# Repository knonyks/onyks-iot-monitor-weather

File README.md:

<span style="font-weight:700;font-size:40px; font-style: italic;">
    Stacja pogodowa
</span>

## Wstęp
Tematem tego projektu jest stacja pogodowa, która zbiera informację odnośnie warunków atmosferycznych i na ich podstawie wysyła dane na oficjalną stronę koła naukowego ONYKS. Stacja ta, mierzy takie wielkości jak poziom CO2, temperaturę, prędkość wiatru, wilgotność itp. (o tym dalej).

## Założenia - jak to ma działać
Dane zbierane są za pomocą odpowiednich czujników a następnie przetwarzane przez mikrokontroler ESP32 - w tym projekcie użyto ESP32-WROOM-32D. Po przetworzeniu dane będą wysyłane na serwer przy użyciu WIFI, a następnie wyświetlane w odpowiedniej rubryce na głównej stronie koła naukowego ONYKS. Planowany rozmiar PCB ***100 mm x 82 mm***.

## Pomiary 

- Pomiar prędkości wiatru - polega na zmierzeniu prędkości obrotowej wału z magnesem, który jest obracany przy użyciu wiatraka. Pomiar ten będzie wykonywany za pomocą **Hallotronu** (czyli na przykład pomiar częstotliwości umownej "1" na czujniku i na podstawie tego określenie prędkości).

- Pomiar ilości opadów - wykonywany w podobny sposób co pomiar prędkości wiatru, z tą różnicą, że wałem kręcą łopatki, o konkretnej objętości. Takie koło wodne wporowadzane jest w ruch kiedy dana łopatka jest wypełniona. Obroty wału z magnesem są szczytywane za pomocą **Hallotronu**. 

- Pomiar kierunku wiatru - odbywa się również za pomocą 4 **Hallotronów** i wału obracanego wiatrowskazem. Tym razem aktywne czujniki wskazują kierunek. Do wskazania będzie 8 kierunków (na przykład pólnoc, południowy wschód itd.).

- Pomiar temperatury oraz wilgotności powietrza - odczytywane dane są z czujnika **DHT22**, który jest zamontowany w obudowie na zewnątrz stacji.

- Pomiar stężenia C02 w atmosferze - odbywa się za pomocą czujnika **SEN0219** znajdującego się bezpośrednio na PCB.

- Pomiar jakości powietrza - polega zastosowaniu czujnika **MQ135**, który jest czuły na Amoniak, gazy Siarczku, opary spowodowane spalaniem Benzenu, oraz potrafi wykrywać dym i innego rodzaju szkodliwe gazy. W czystym powietrzu czujnik ten ma niską przewodność, rośnie wraz z pojawieniem się w atmosferze substancji szkodliwych

## Obudowy oraz elementy mechaniczne

- Obudowy, będą zaprojektowane w oprogramowaniu CAD a następnie wyprodukowane za pomocą druku 3D. 

- Wały i łożyska będą kupowane w sklepie modelarskim np. *https://sklep.modelarnia.pl/*, lub budowalnym takim jak OBI czy CASTORAMA.

- Wiatrak i koło wodne będą zaprojektowane w oprogramowaniu CAD, a następnie drukowane.

- Do **Hallotronów** będą użyte drobne magnesy Neodymowe

## Schematy blokowe

###  Położenie elementów na płytce drukowanej :

###  Ogólny schemat ideowy układu :

## Link do rozpiski z elementami
Tutaj stworzony jest wykaz elementów potrzebnych do złożenia danej stacji : 
https://docs.google.com/spreadsheets/d/16E9U7lwzSHfPhs8wRjM2mrblf8zyNPCpttjlwKn6Azs/edit?usp=sharing

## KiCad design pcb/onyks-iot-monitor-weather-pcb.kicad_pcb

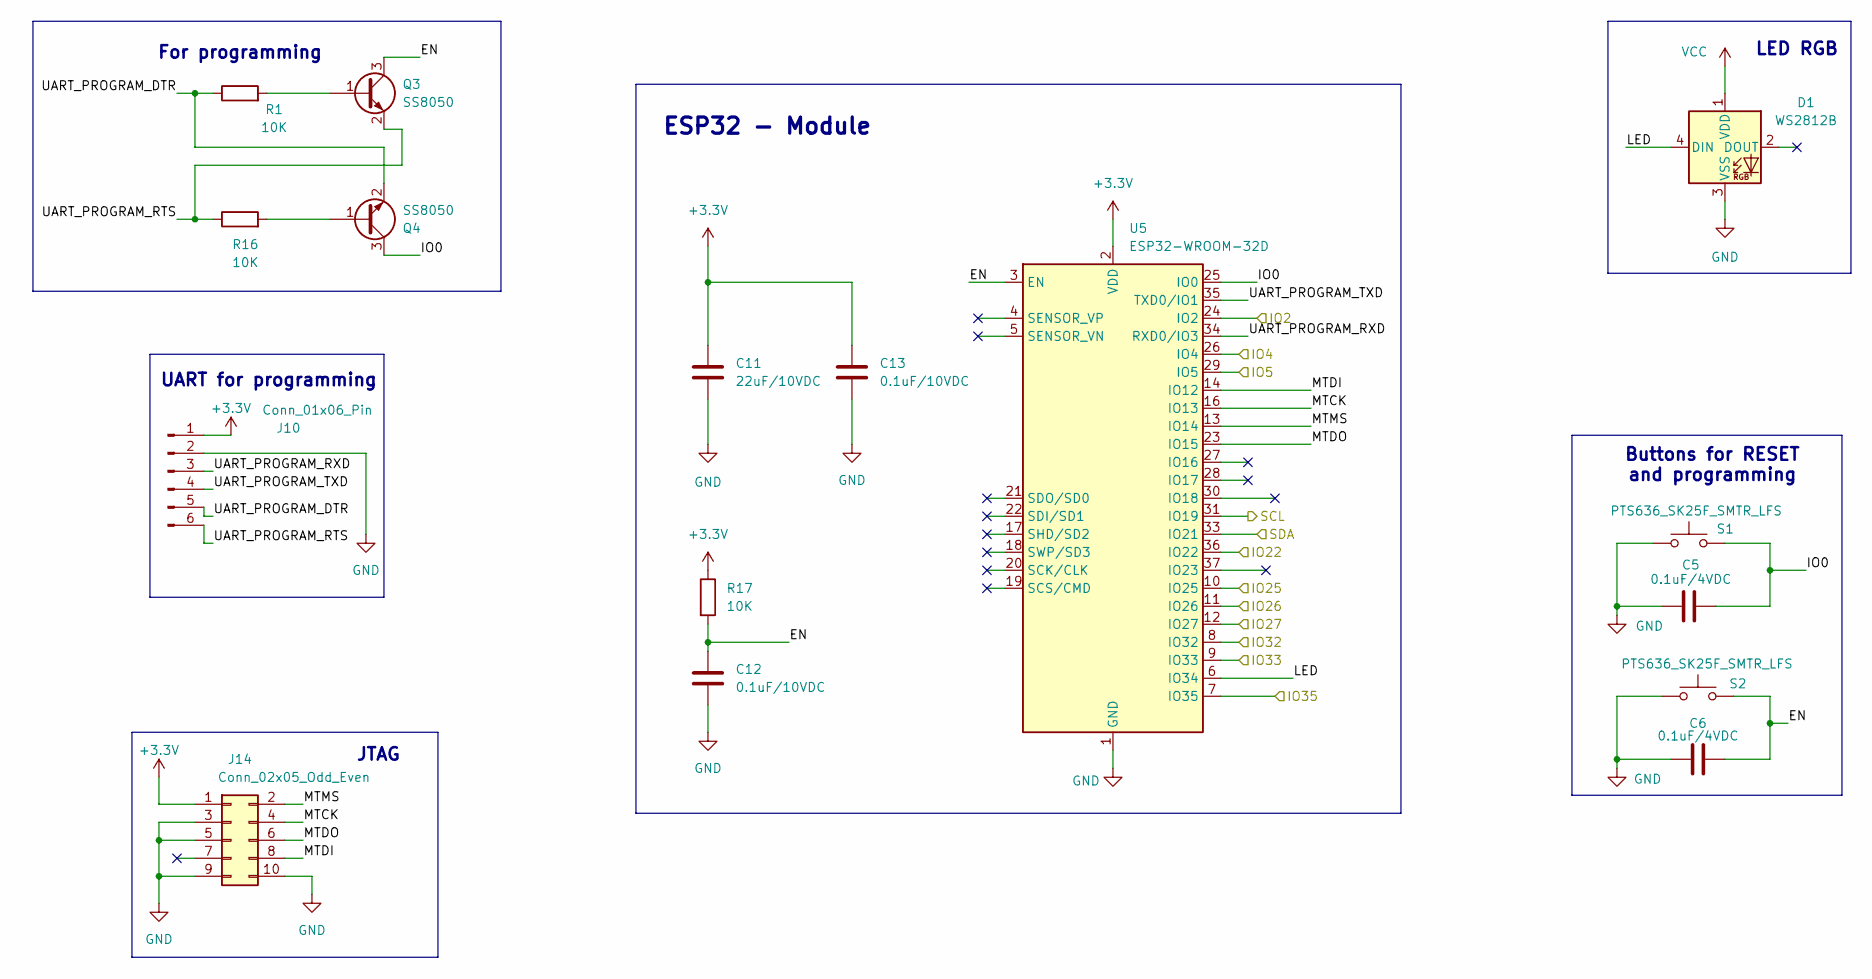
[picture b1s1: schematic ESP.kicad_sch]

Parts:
C5, C6: 0.1uF/4VDC; C_0603_1608Metric
C11: 22uF/10VDC; C_0603_1608Metric
C12, C13: 0.1uF/10VDC; C_0603_1608Metric
D1: WS2812B; LED_WS2812B_PLCC4_5.0x5.0mm_P3.2mm
J10: Conn_01x06_Pin; PinHeader_1x06_P2.54mm_Vertical
J14: Conn_02x05_Odd_Even; PinHeader_2x05_P2.54mm_Vertical
Q3, Q4: SS8050; SOT-23
R1, R16, R17: 10K; R_0603_1608Metric
S1, S2: PTS636_SK25F_SMTR_LFS; PTS636SK25FSMTRLFS; Mouser Part Number 611-PTS636SK25FSMTRL
U5: ESP32-WROOM-32D

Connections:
+3.3V: C11.1, C13.1, J10.1, J14.1, R17.1, U5.2 (VDD); also elsewhere on the board
/ESP32/EN: C6.2, C12.1, Q3.3 (C), R17.2, S2.2, U5.3 (EN)
/ESP32/IO0: C5.2, Q4.3 (C), S1.2, U5.25 (IO0)
/ESP32/IO2: U5.24 (IO2); also elsewhere on the board
/ESP32/IO4: U5.26 (IO4); also elsewhere on the board
/ESP32/IO5: U5.29 (IO5); also elsewhere on the board
/ESP32/IO22: U5.36 (IO22); also elsewhere on the board
/ESP32/IO25: U5.10 (IO25); also elsewhere on the board
/ESP32/IO26: U5.11 (IO26); also elsewhere on the board
/ESP32/IO27: U5.12 (IO27); also elsewhere on the board
/ESP32/IO32: U5.8 (IO32); also elsewhere on the board
/ESP32/IO33: U5.9 (IO33); also elsewhere on the board
/ESP32/IO35: U5.7 (IO35); also elsewhere on the board
/ESP32/LED: D1.4 (DIN), U5.6 (IO34)
/ESP32/MTCK: J14.4, U5.16 (IO13)
/ESP32/MTDI: J14.8, U5.14 (IO12)
/ESP32/MTDO: J14.6, U5.23 (IO15)
/ESP32/MTMS: J14.2, U5.13 (IO14)
/ESP32/SCL: U5.31 (IO19); also elsewhere on the board
/ESP32/SDA: U5.33 (IO21); also elsewhere on the board
/ESP32/UART_PROGRAM_DTR: J10.5, Q4.2 (E), R1.1
/ESP32/UART_PROGRAM_RTS: J10.6, Q3.2 (E), R16.1
/ESP32/UART_PROGRAM_RXD: J10.3, U5.34 (RXD0/IO3)
/ESP32/UART_PROGRAM_TXD: J10.4, U5.35 (TXD0/IO1)
GND: C5.1, C6.1, C11.2, C12.2, C13.2, D1.3 (VSS), J10.2, J14.3, J14.5, J14.9, J14.10, S1.1, S2.1, U5.1 (GND), U5.15 (GND), U5.38 (GND), U5.39 (GND); also elsewhere on the board
unnamed: Q3.1 (B), R1.2
unnamed: Q4.1 (B), R16.2
VCC: D1.1 (VDD); also elsewhere on the board

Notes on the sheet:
ESP32 - Module
JTAG
UART for programming
LED RGB
Buttons for RESET and programming
For programming

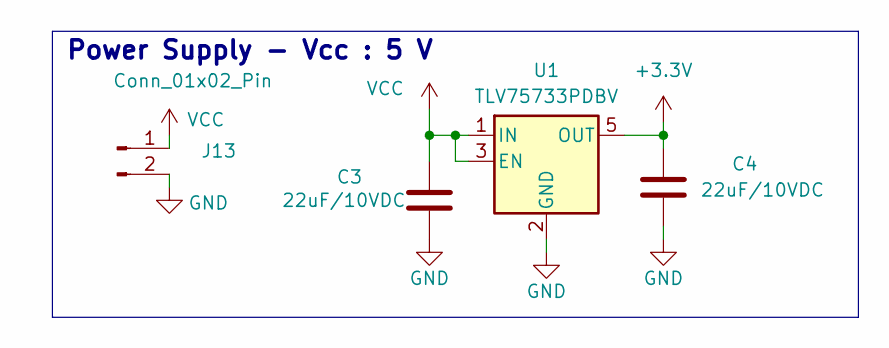
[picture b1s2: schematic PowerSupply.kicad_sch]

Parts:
C3, C4: 22uF/10VDC; C_0603_1608Metric
J13: Conn_01x02_Pin; PinHeader_1x02_P2.54mm_Vertical
U1: TLV75733PDBV; SOT-23-5

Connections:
+3.3V: C4.1, U1.5 (OUT); also elsewhere on the board
GND: C3.2, C4.2, J13.2, U1.2 (GND); also elsewhere on the board
VCC: C3.1, J13.1, U1.1 (IN), U1.3 (EN); also elsewhere on the board

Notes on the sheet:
Power Supply - Vcc : 5 V

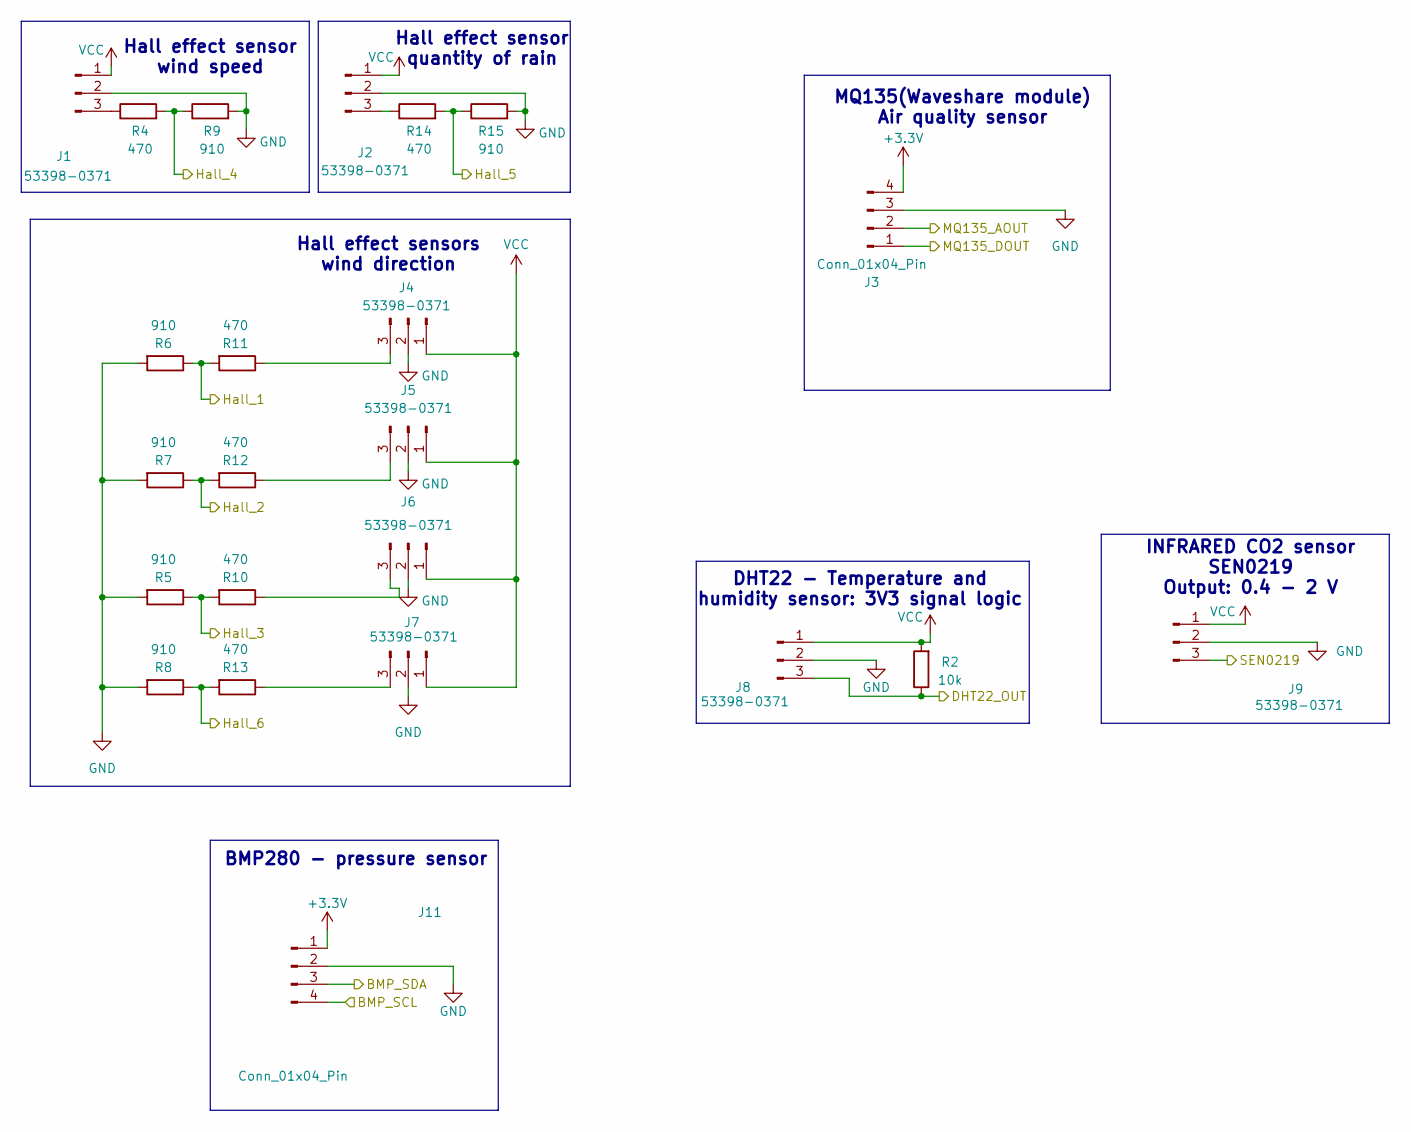
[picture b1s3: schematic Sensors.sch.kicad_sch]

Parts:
J1, J2, J4, J5, J6, J7, J8, J9: 53398-0371; PinHeader_1x03_P2.54mm_Vertical; Manufacturer_Part_Number 53398-0371
J3, J11: Conn_01x04_Pin; PinHeader_1x04_P2.54mm_Vertical
R2: 10k; R_0603_1608Metric
R4, R10, R11, R12, R13, R14: 470; R_0603_1608Metric
R5, R6, R7, R8, R9, R15: 910; R_0603_1608Metric

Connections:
+3.3V: J3.4, J11.1; also elsewhere on the board
/ESP32/IO2: J3.2; also elsewhere on the board
/ESP32/IO4: J8.3, R2.1; also elsewhere on the board
/ESP32/IO5: J9.3; also elsewhere on the board
/ESP32/IO22: J3.1; also elsewhere on the board
/ESP32/IO25: R6.1, R11.2; also elsewhere on the board
/ESP32/IO26: R7.1, R12.2; also elsewhere on the board
/ESP32/IO27: R5.1, R10.2; also elsewhere on the board
/ESP32/IO32: R4.2, R9.1; also elsewhere on the board
/ESP32/IO33: R8.1, R13.2; also elsewhere on the board
/ESP32/IO35: R14.2, R15.1; also elsewhere on the board
/ESP32/SCL: J11.4; also elsewhere on the board
/ESP32/SDA: J11.3; also elsewhere on the board
GND: J1.2, J2.2, J3.3, J4.2, J5.2, J6.2, J7.2, J8.2, J9.2, J11.2, R5.2, R6.2, R7.2, R8.2, R9.2, R15.2; also elsewhere on the board
unnamed: J1.3, R4.1
unnamed: J2.3, R14.1
unnamed: J4.3, R11.1
unnamed: J5.3, R12.1
unnamed: J6.3, R10.1
unnamed: J7.3, R13.1
VCC: J1.1, J2.1, J4.1, J5.1, J6.1, J7.1, J8.1, J9.1, R2.2; also elsewhere on the board

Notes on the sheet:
Hall effect sensors wind direction
INFRARED CO2 sensor SEN0219 Output: 0.4 - 2 V
BMP280 - pressure sensor
DHT22 - Temperature and humidity sensor: 3V3 signal logic
MQ135(Waveshare module) Air quality sensor
Hall effect sensor wind speed
Hall effect sensor quantity of rain

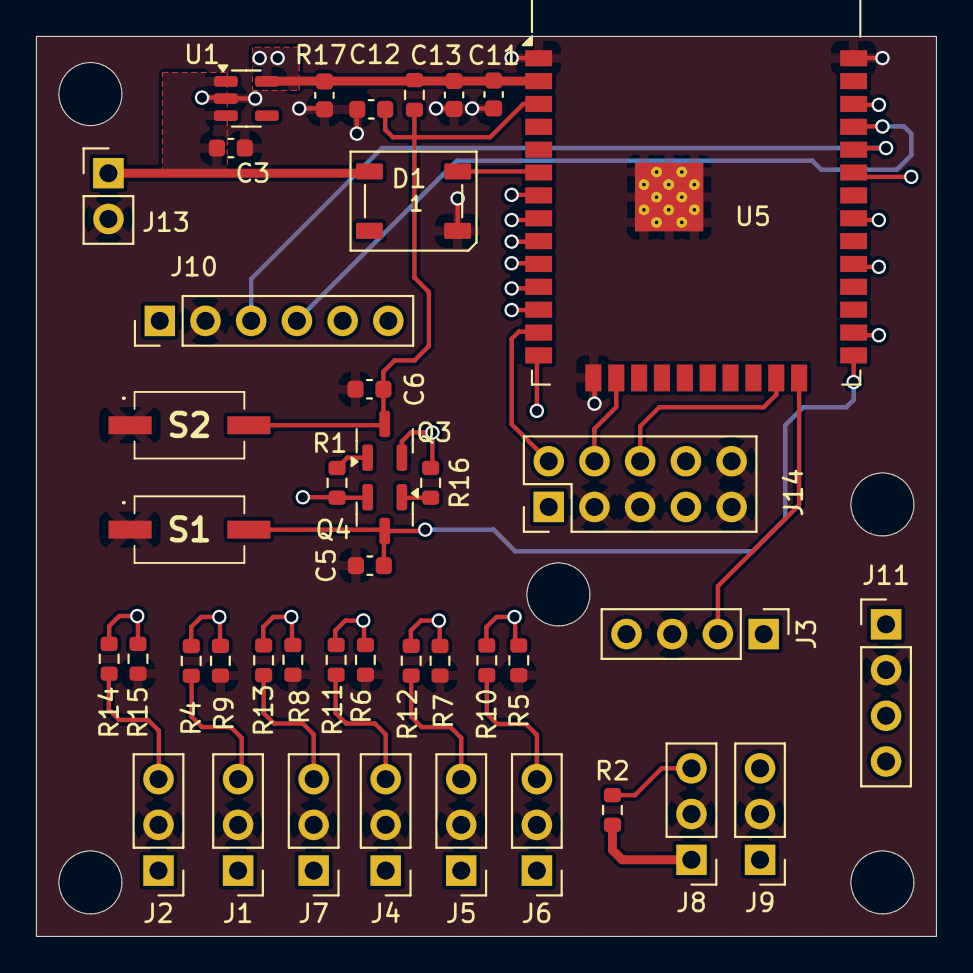
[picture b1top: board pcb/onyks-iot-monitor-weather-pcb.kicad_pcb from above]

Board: 4 copper layers, 50.0 x 50.0 mm, 43 parts (0 on the bottom side), 34 nets.

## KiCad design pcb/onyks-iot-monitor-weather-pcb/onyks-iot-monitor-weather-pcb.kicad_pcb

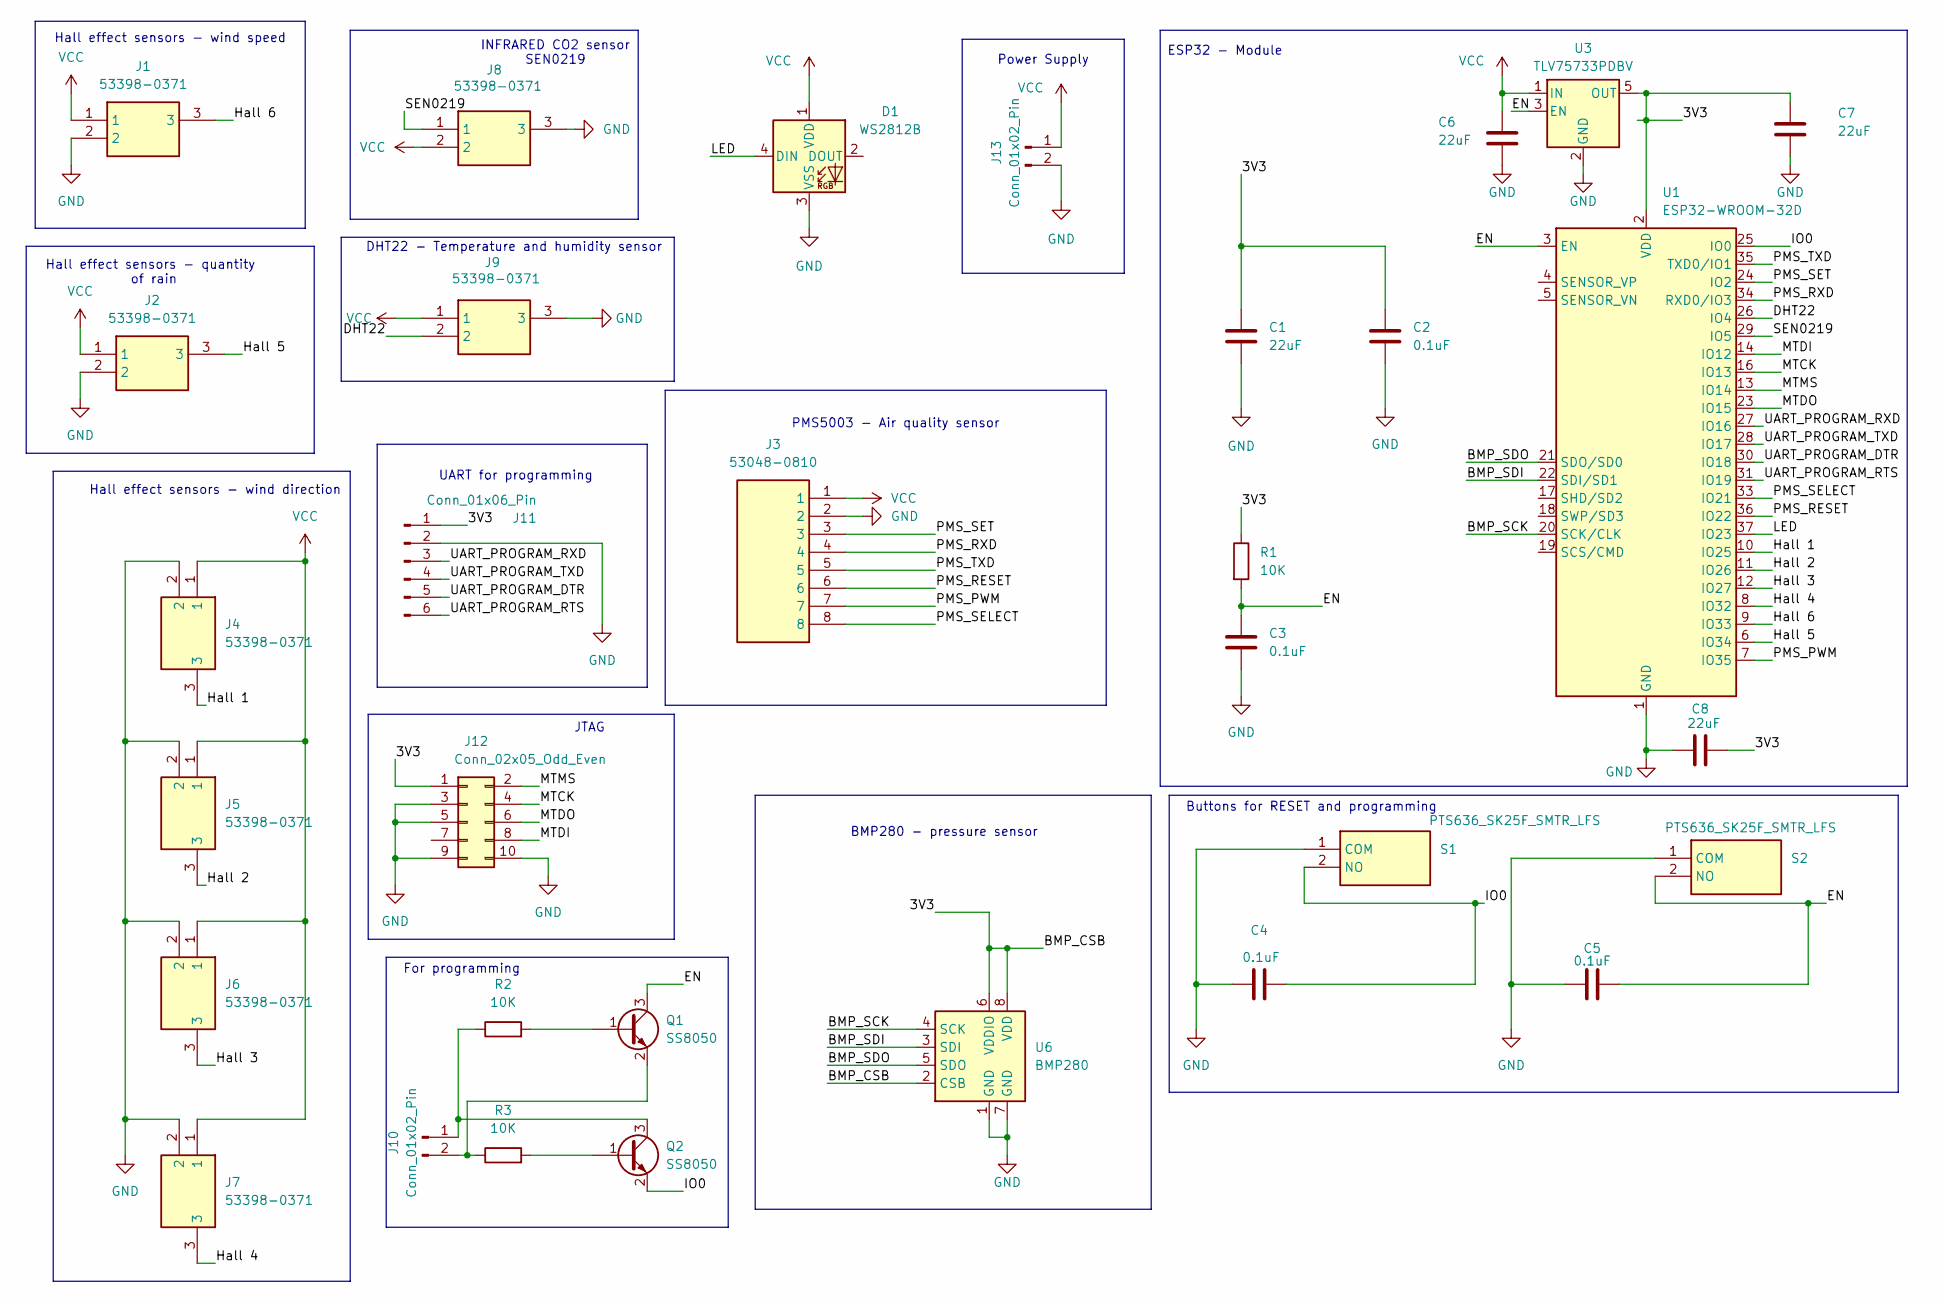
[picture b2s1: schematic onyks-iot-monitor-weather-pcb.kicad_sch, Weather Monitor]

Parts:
C1, C6, C7, C8: 22uF; C_0603_1608Metric
C2, C3, C4, C5: 0.1uF; C_0603_1608Metric
D1: WS2812B; LED_WS2812B_PLCC4_5.0x5.0mm_P3.2mm
J1, J2, J4, J5, J6, J7, J8, J9: 53398-0371; Manufacturer_Part_Number 53398-0371
J3: 53048-0810; 530480810; Manufacturer_Part_Number 53048-0810
J10, J13: Conn_01x02_Pin; PinHeader_1x02_P2.54mm_Vertical
J11: Conn_01x06_Pin; PinHeader_1x06_P2.54mm_Vertical
J12: Conn_02x05_Odd_Even; PinHeader_2x05_P2.54mm_Vertical
Q1, Q2: SS8050; SOT-23
R1, R2, R3: 10K; R_0603_1608Metric
S1, S2: PTS636_SK25F_SMTR_LFS; PTS636SK25FSMTRLFS; Mouser Part Number 611-PTS636SK25FSMTRL
U1: ESP32-WROOM-32D
U3: TLV75733PDBV; SOT-23-5
U6: BMP280; Bosch_LGA-8_2x2.5mm_P0.65mm_ClockwisePinNumbering

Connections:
/3V3: C1.1, C2.1, C7.1, C8.2, J11.1, J12.1, R1.1, U1.2 (VDD), U3.5 (OUT), U6.2 (CSB), U6.6 (VDDIO), U6.8 (VDD)
/BMP_SCK: U1.20 (SCK/CLK), U6.4 (SCK)
/BMP_SDI: U1.22 (SDI/SD1), U6.3 (SDI)
/BMP_SDO: U1.21 (SDO/SD0), U6.5 (SDO)
/DHT22: J9.2, U1.26 (IO4)
/EN: C3.1, C5.2, Q1.3 (C), R1.2, S2.2 (NO), U1.3 (EN), U3.3 (EN)
/Hall 1: J4.3, U1.10 (IO25)
/Hall 2: J5.3, U1.11 (IO26)
/Hall 3: J6.3, U1.12 (IO27)
/Hall 4: J7.3, U1.8 (IO32)
/Hall 5: J2.3, U1.6 (IO34)
/Hall 6: J1.3, U1.9 (IO33)
/IO0: C4.2, Q2.2 (E), S1.2 (NO), U1.25 (IO0)
/LED: D1.4 (DIN), U1.37 (IO23)
/MTCK: J12.4, U1.16 (IO13)
/MTDI: J12.8, U1.14 (IO12)
/MTDO: J12.6, U1.23 (IO15)
/MTMS: J12.2, U1.13 (IO14)
/PMS_PWM: J3.7, U1.7 (IO35)
/PMS_RESET: J3.6, U1.36 (IO22)
/PMS_RXD: J3.4, U1.34 (RXD0/IO3)
/PMS_SELECT: J3.8, U1.33 (IO21)
/PMS_SET: J3.3, U1.24 (IO2)
/PMS_TXD: J3.5, U1.35 (TXD0/IO1)
/SEN0219: J8.1, U1.29 (IO5)
/UART_PROGRAM_DTR: J11.5, U1.30 (IO18)
/UART_PROGRAM_RTS: J11.6, U1.31 (IO19)
/UART_PROGRAM_RXD: J11.3, U1.27 (IO16)
/UART_PROGRAM_TXD: J11.4, U1.28 (IO17)
GND: C1.2, C2.2, C3.2, C4.1, C5.1, C6.2, C7.2, C8.1, D1.3 (VSS), J1.2, J2.2, J3.2, J4.2, J5.2, J6.2, J7.2, J8.3, J9.3, J11.2, J12.3, J12.5, J12.9, J12.10, J13.2, S1.1 (COM), S2.1 (COM), U1.1 (GND), U1.15 (GND), U1.38 (GND), U1.39 (GND), U3.2 (GND), U6.1 (GND), U6.7 (GND)
unnamed: J10.1, Q2.3 (C), R2.1
unnamed: J10.2, Q1.2 (E), R3.1
unnamed: Q1.1 (B), R2.2
unnamed: Q2.1 (B), R3.2
VCC: C6.1, D1.1 (VDD), J1.1, J2.1, J3.1, J4.1, J5.1, J6.1, J7.1, J8.2, J9.1, J13.1, U3.1 (IN)

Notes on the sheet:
For programming
JTAG
PMS5003 - Air quality sensor
INFRARED CO2 sensor SEN0219
Hall effect sensors - wind speed
Buttons for RESET and programming
BMP280 - pressure sensor
ESP32 - Module
Hall effect sensors - wind direction
Power Supply
UART for programming
DHT22 - Temperature and humidity sensor
Hall effect sensors - quantity of rain

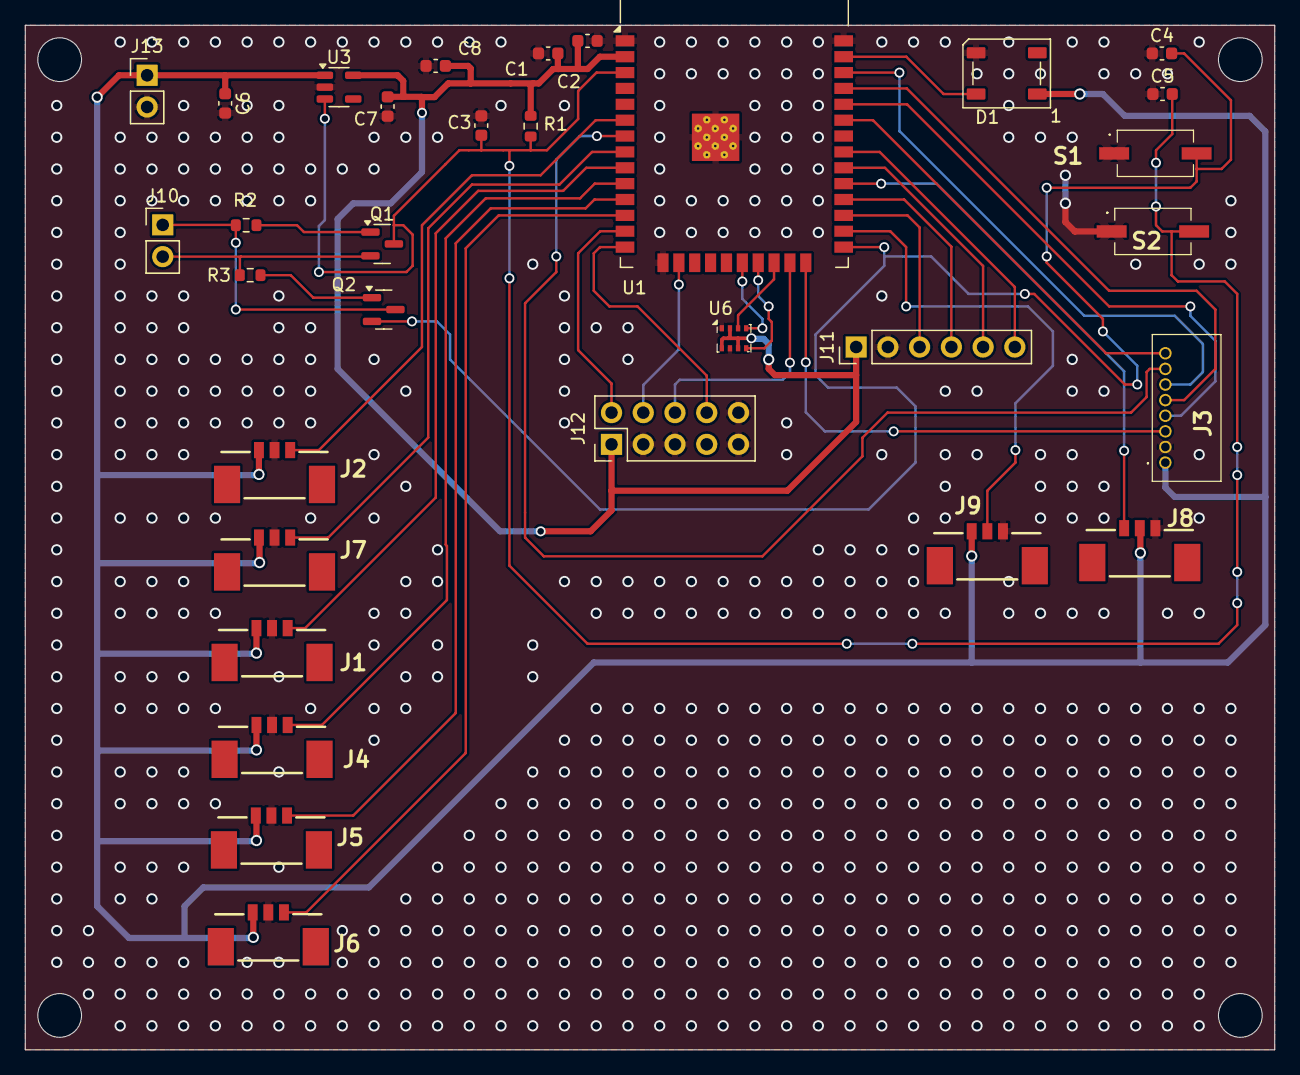
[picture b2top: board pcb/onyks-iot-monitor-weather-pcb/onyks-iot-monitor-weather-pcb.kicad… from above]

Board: 2 copper layers, 100.0 x 82.0 mm, 32 parts (0 on the bottom side), 35 nets.

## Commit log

2024-11-14 Added Readme. Created pcb blank project
2024-11-17 Added Docs for sensors and esp32wroom32d
2024-11-17 Added spreadsheet link to readme
2024-11-18 basic PCB template layout from the last meeting
2024-11-24 Added schematic for our project
2024-12-01 Updated schematics and added footprints and 3dmodels for the elements
2024-12-02 Added PCBv1.0
2024-12-08 Updated schematic, changed and added couple of elements: 1.Changed buttons; 2.Changed Voltage Regulator; 3.Changed LED; 4.Added JTAG interface; 5.Added UART for programming; 6.Added other elements li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
2024-12-16 Done my version of PCB
2024-12-17 Few corrections, small ammount of parts were not connected to the ground.
2025-01-03 Changed ground planes, and overall small changes
2025-02-19 CheckedJLCPCBDesignRules, the only remaining errors are due to holes in esp 32 module
2025-02-20 Mistake Correction
2025-02-26 U6,J3 ground pads are not connected to the ground zone automatically(due to their footprints). Ground pads C2 and C1 are connected to the ground plane via route. Overall little changes in layout. Gro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
2025-02-28 Changed c1 c2 positions
2025-02-28 Design Rules - Thermal relief problem partially solved
2025-02-28 beta v1
2025-04-22 Aded Readme, change schematic layout, added block diagrams
2025-06-20 Poprawki w schemacie elektrycznym
2025-06-23 Dalsze zmiany w schemacie elektrycznym - przewidywane duże zmiany w PCB
2025-07-01 Dodanie schematu pdf
2025-07-05 Struktura hierarchiczna
2025-07-15 Drobne poprawki w schemacie elektrycznym
2025-07-15 poprawiony schemat w pdf
2025-07-28 zrobiony PCB
2025-07-28 PCB poprawki, oraz znowe zrzut ekranu z PCB
2025-07-28 Rename PCBDimensions.png to PCBDimensions2.png
2025-08-05 PCB poprawione
2025-08-24 PCB jeszcze mniejsza wersja
2025-08-30 4 layer PCB
2025-08-30 readme change - new 4 layer PCB image
2025-10-06 gerbery dodane do folderu fabrication
2025-11-02 zip do greberów
2025-11-19 dodanie zapomnianych plików drill
2026-04-15 obudowa v1 pierwszy commit
2026-04-15 komponenty .step
2026-04-17 v1 case in progres1
2026-04-22 yaml
